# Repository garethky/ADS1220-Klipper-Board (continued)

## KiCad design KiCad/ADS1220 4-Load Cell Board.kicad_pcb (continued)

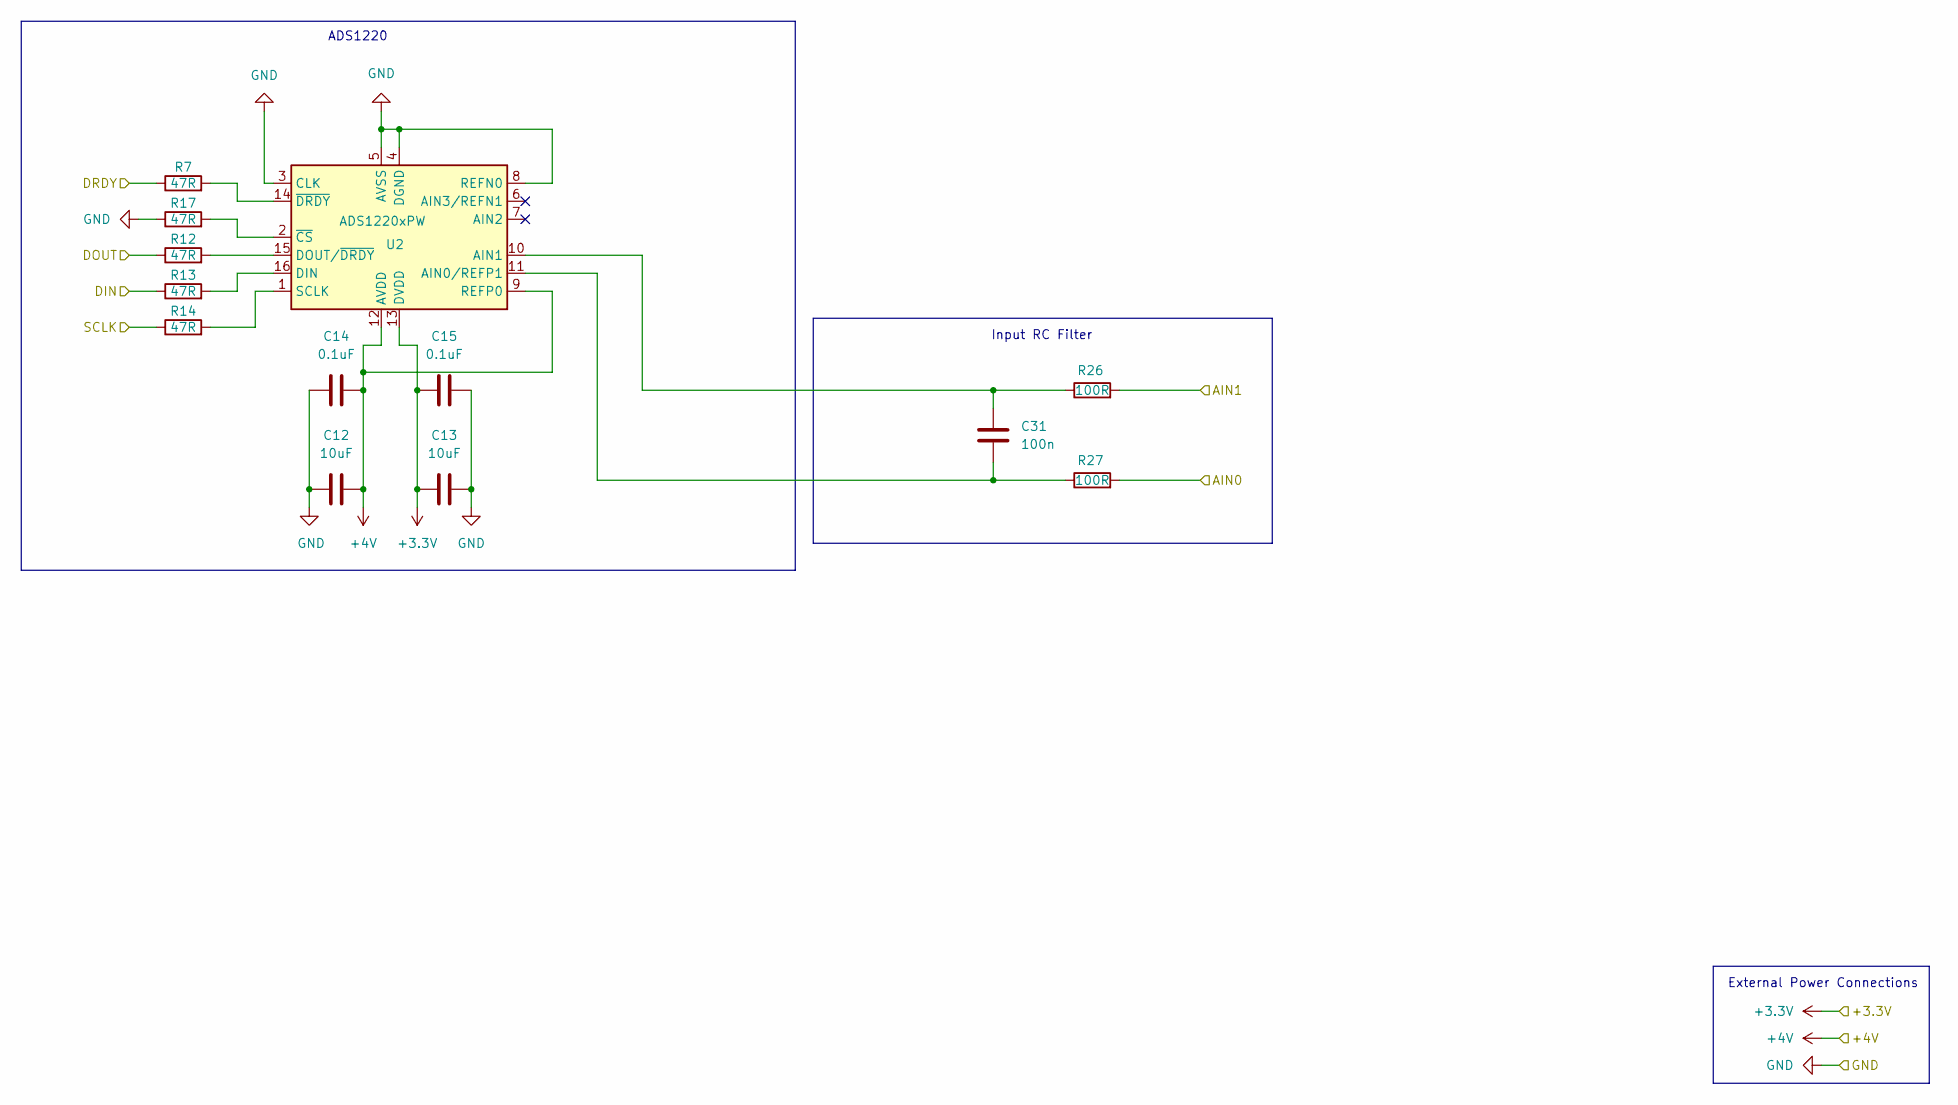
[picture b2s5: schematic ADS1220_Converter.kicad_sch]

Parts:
C12, C13: 10uF; C_0805_2012Metric_Pad1.18x1.45mm_HandSolder
C14, C15: 0.1uF; C_0805_2012Metric_Pad1.18x1.45mm_HandSolder
C31: 100n; C_0805_2012Metric_Pad1.18x1.45mm_HandSolder
R7, R12, R13, R14, R17: 47R; R_0805_2012Metric_Pad1.20x1.40mm_HandSolder
R26, R27: 100R; R_0805_2012Metric_Pad1.20x1.40mm_HandSolder
U2: ADS1220xPW; TSSOP-16_4.4x5mm_P0.65mm

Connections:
/ADS1220 AD Converter/AIN0: R27.2; also elsewhere on the board
/ADS1220 AD Converter/AIN1: R26.2; also elsewhere on the board
/ADS1220 AD Converter/DIN: R13.1; also elsewhere on the board
/ADS1220 AD Converter/DOUT: R12.1; also elsewhere on the board
/ADS1220 AD Converter/DRDY: R7.1; also elsewhere on the board
/ADS1220 AD Converter/SCLK: R14.1; also elsewhere on the board
unnamed 39: C31.2, R27.1, U2.11 (AIN0/REFP1); also elsewhere on the board
unnamed 40: C31.1, R26.1, U2.10 (AIN1); also elsewhere on the board
unnamed: R13.2, U2.16 (DIN)
unnamed: R12.2, U2.15 (DOUT/~DRDY)
unnamed: R14.2, U2.1 (SCLK)
unnamed: R17.2, U2.2 (~CS)
unnamed: R7.2, U2.14 (~DRDY)

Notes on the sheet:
ADS1220
Input RC Filter
External Power Connections

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
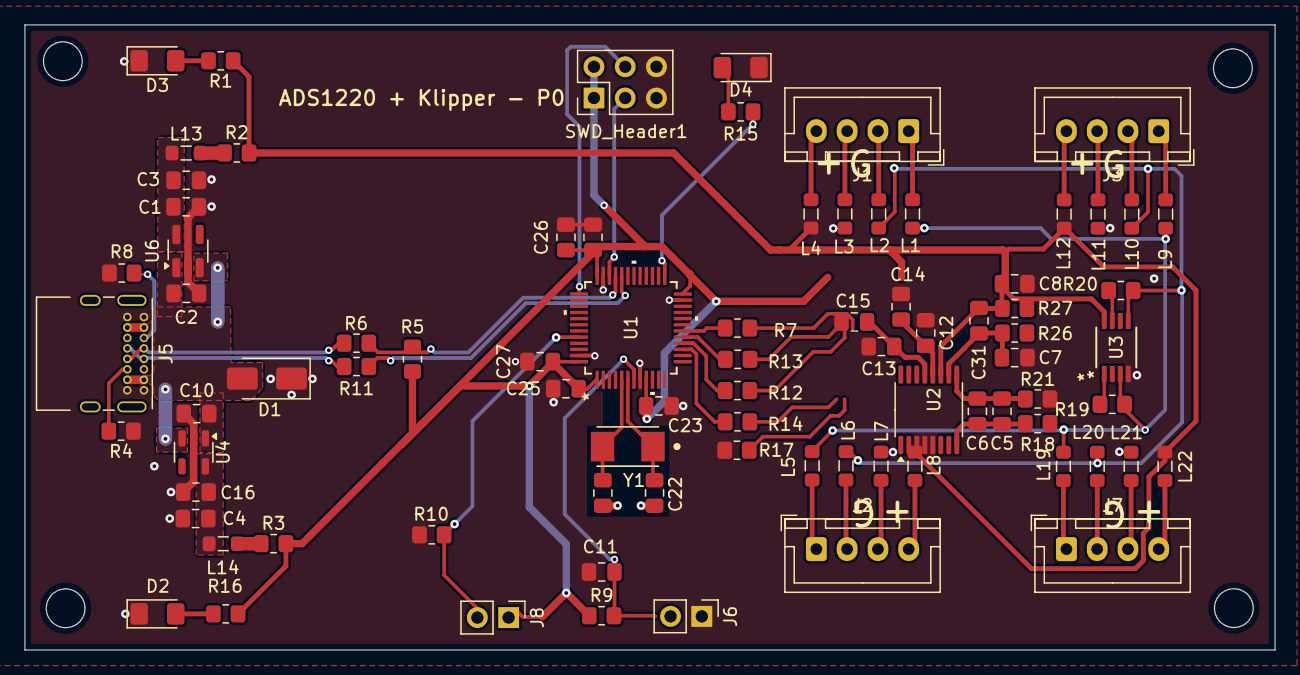
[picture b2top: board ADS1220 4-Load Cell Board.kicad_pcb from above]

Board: 2 copper layers, 101.6 x 50.8 mm, 82 parts (0 on the bottom side), 57 nets.

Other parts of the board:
C3, C4, C5, C6: 10uF; C_0805_2012Metric_Pad1.18x1.45mm_HandSolder
C7, C8: 0.1uF; C_0805_2012Metric_Pad1.18x1.45mm_HandSolder
D3: LED; LED_1206_3216Metric_Pad1.42x1.75mm_HandSolder
R1: 1K; R_0805_2012Metric_Pad1.20x1.40mm_HandSolder
R2, R3: 0R; R_0805_2012Metric_Pad1.20x1.40mm_HandSolder
R18, R21: 100R; R_0805_2012Metric_Pad1.20x1.40mm_HandSolder

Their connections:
unnamed: D3.2 (A), R1.2
unnamed 37: R2.1; also elsewhere on the board
unnamed 39: C8.1; also elsewhere on the board
unnamed 40: C7.2; also elsewhere on the board
unnamed 46: C4.1; also elsewhere on the board
unnamed 47: C3.1; also elsewhere on the board

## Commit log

2024-08-15 Add KiCad Project Files
2024-08-15 Add MCP6V92 Amplifier
    Add amplifier part to amplifier block
2024-08-15 Add bypass resistors for Amplifier
    Add 0R resistor pads to allow the amplifier to be bypassed so we can test with/without it in the circuit.
2024-08-17 Use 12V Power
    * Use 12 V Power
    * Update to an F103 processor with better compatibility with Katapult
2024-08-18 Update 5V Power Stage
    * Update the 5V power stage based on the recommendations from TI.
    * Updated standard passive footprint to 0805 hand solder configuration
2024-08-19 Initial Routing
    Taking a first pass at layout of the PCB
    * load cell connectors were moved to the root schematic and placed on a bus to facilitate PCB routing
    * Nets for the filters were directly connected to remove the confusion about GND verses REFN
2024-08-20 Fix amplifier footprint
    shrink pads to they can be produced on 0.2mm process
2024-08-20 Cleanup Files
    * delete unused plots
    * block lock files from git
2024-08-20 Update USB Connector
    Update USB connector and design rules so it passes inspection.
2024-08-20 Update Switch Footprints
    Update switch schematic and footprint to match the actual part being used
2024-08-20 Update Crystal
    Change crystal footprint to ABM3-8.000MHZ-B4Y-T
2024-08-20 PDF Schematic Update
2024-08-20 Update Inductor Footprint
    Update to PA4332.222NLT
2024-08-20 Readme update
2024-08-21 Convert Power to LDOs
    Convert power section to use only LDOs. This means we will only get 4.75V or 4.5V on the analog line but this comes with greatly increased simplicity of layout.
2024-08-21 Update PDF & Board Image
2024-08-22 Add Single Wire Debug
    * Add Single Wire Debug (SWD) Tag Connect Connector
    * Re-layout of 5V power so the 5V pins connect to a pad directly behind the USB connector
    * Add 0R resistors to air gap the 3.3V and 5V power rails for incremental board bringup
    * Rotate ADS1220 for cleaner layout
    * Remove connections to reference voltage pins, since AVDD/AVSS is a valid reference
    fixup
2024-08-23 USB Improvements
    * Changed the USB connector symbol and rebuilt it to have pins that match the pads
    * Set up the USB lines as a differential pair
    * VIA Stitch the board
    * Increased minimum trace width to 0.3mm
2024-08-24 Crystal Changes
    * Update crystal selection, schematic and footprint
    * Add resistor to limit drive current to crystal
    * Block ground plane fill under crystal circuit
2024-08-24 Update Rext value
    1.1k is an approximate value for the resistance required.
2024-08-24 Re-add Via Stitching
2024-12-23 Initial commit of High Temp Board
2024-12-23 Work In Progress
    moving towards v 2
2024-12-23 High Temp Toolhead Board
    * Move different boards to directories
    * check in the High Temp Tool Board work
    delete autosaves
2024-12-24 Fix Incorrect Power Connections to ADXL or Gate
    GND and VIN were reversed
2024-12-31 Re-work PCB for Grids
    * Lay out components consistently using a 0.2mm grid
    * Removes all grids that are not divisible by 0.1mm (gets rid of 'off by 0.05 errors')
    * Brought back some more dense layouts with rows of components
    * Reset all reference text positions so they align with components consistently
    * References don't intersect with vias
    * Improve how some traces enter/exit the chips using smaller vias and traces
2024-12-31 Filet Edgecuts
    Makes corners of the board have a 4mm radius
2024-12-31 Cleanup Zone Fills
    * Cleaned up the zone fills and component positioning for the LDOs. Now they are on the grid and identical copies of each other
    * Added a pad on layers 2, 3 & 4 under the no-connect pad 5 on the switching regulator for better thermal transfer.
    * Cleaned up some ground pours around the MCU. Some traces caused islands or choking of the ground pins.
    * Tweaked some text placement to better avoid vias and be less ambiguous
    * Earth Protective zone now removes islands.
    * Eliminated a choked zone in the 3.3V power plane by routing ADS1220_DRDY on both layer 2 and 3. Since this isn't a high speed signal this should be fine.
2024-12-31 L1 GND Tweaks
    * Disable all islands in the ground fill zone. This makes it much easier to spot and fix them.
    * Fixed ground island near the ADS1220 reference lines.
    * Fixed ground island at the OR gate near the ADXL345
2025-01-02 Stencil Registration
    Add holes in the paste layer that match the PCB mounting holes to make registration with the PCB easier.
2025-01-02 Add Fan LEDs
    * Add LEDs for both fans
    * Reposition Earth to GND Diode to bottom of board for more LED space
    * Re-run the via stitching, this time assuming tented vias can have solder mask on them
    * Solved a problem with zone clearances, set all zone clearances to 0
2025-01-02 Minor Updates
    * Tweak ground plane min connection size to 0.2mm to improve the areas it can reach
    * Updates to the ADS1220 layout
    * Updates to the decoupling capacitors around the MCU
2025-01-04 Add USB C Connector
    The commit adds a USB C connector to the back side of the board.
    * This can be used to bench run and test the board without the 24V power supply.
    * Its not designed to be used with the printer is operational, thats what the main connector is for
    * All components are optional and can be omitted
    * Reverse current protection diodes are included to stop current backfeeding into the USB Host in operation
    Other updates:
2025-01-04 Add Open Source Hardware Logo
    logo ++
2025-01-05 Add Net Class Directives
    This change adds Net Class Directives for 3 types of specialized nets:
    * ADC Signal - a net that may potentially be sensed by an ADC and should be treated as 50 Ohm impedance
    * Digital Signal - a net that will have an oscillating digital signal on it but does not carry any power. This should also be treated as 50 Ohm impedance.
    * Digital Pair - a differential digital pair. This is only used for the USB data pair which is 90 Ohm impedance.
2025-01-05 Tweaks to U4 Layout
    Rotate u4 90 degrees and move the SPI clock line down to layer 3
    Fix oscillator missing 3d model
2025-01-07 More Targeted GND Paths
    * Fix the TLVM23615RDNR footprint so its pads are plated
    * Add GND vias in locations where via walls exist on layer 1
    * Add GND vias or where a signal transitions across the core material between layer 2 and 3
    * Add some GND vias near power decoupling capacitors
    * Move the ADS1220 ADC signal lines down to layer 32 so they have 100% ground coverage across their length. They were passing under 5V caps and resistors.
2025-01-08 USB Routing Improvement & Trach Width Change
    * Fix net class assignment of USB lines so they autoroute with the correct rules.
    * Moved the LED CLK line routing so it doesn't cross the USB lines
    * Added a zone of ground fill on layer 3 to cover the USB traces on the back of the board
    * Changes the standard track with to 15mil / 0.381mm. This is what OSH Park say is 50 Ohm in their process.
    Fixup
    Fixup
2025-01-10 Replace Oscillator Module with Crystal
    * After a bunch of research I've concluded that I cant use the Oscillator Module with Katapult's codebase for the STM32 chips. Added discussion on this to the design doc. Updated design to use a crys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
    * Based on the best advice I can find for decoupling capacitors on the MCU I have moved them to the back side of the board. This allows their footprints to overlap with the MCU itself, reducing the d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
2025-01-10 Add Via Stitching
    * Re-run via stitching on GND
    * Add capacitor values to crystal caps
    * Update design doc
    * Remove bad assembly document
2025-01-14 WIP Address community comments
    * Switch to 6 layers and update design rules for new 6 layer process
    * Change fan MOSFETs based on feedback. Drive MOSFETs with level shifter at 5V
    * Add a 5V LDO for the loadcell thats not potentially poisoned by 5V LED noise
    * Delete MAX chip, switch to PT1000
    * Use 2 SPI busses, delete CS lines
    * Move all components to front of board, re-organize layout to fit everything
2025-01-19 Feedback Updates Completed
    * Disconnected unused GPIO pins from ground, use software pulldown instead.
    * Re-rout for OSHPark's 6 layer stackup
    * Shrink reference text to 0.8mmx0.8mm and 5 mil thickness
2025-01-22 Update 5V Power input
    * Changed 5V USB power to rout in via the main 24V power input. This assumes the buck converter can operate in dropout mode and pass the 5V supply to the LDOs. This avoids potential issues with backf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
    * Added a klipper pins file to give meaningful names to pins
    * Added do-not-populate bypass resistors for fans to test tachometer behavior
2025-01-22 Add Thermal Reliefs
    * Enable thermal relief on GND and 3.3V
    * Re-work 5.5V zone to support thermal relief
    * Move vias off of silkscreen
    * Fix vias that are close to pads
2025-01-23 Add Dotstar Indicator
    This change replaces the indicator LED with a Dotstar RGB LED. This allows various conditions to be indicated at the toolhead via colors, brightness and blinking.
    * Fixed missing guard ring on layers 4 and 5.
2025-01-23 Minor Track Tweaking
    Just making sure tracks clear vias and everything looks manufacturable.
2025-01-24 Move Filament Switch & Heatbreak Thermistor to ADC Inputs
    * Move Filament switch line from PA15 to PA7
    * Move Heatberak Thermistor from PB1 to PA6 (PB1 is Boot1)
    * Re-routed Filament switch line on the back side of the PCB
    * Edited pin assignments for thermistors to make routing cleaner
    * Updated pins file to reflect changes
    * Renamed Neopixel port to Dotstar.
2025-01-26 Update Docs
    small doc updates
